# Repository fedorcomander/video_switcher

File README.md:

# video_switcher
4 channel FPV video switcher

Components: ATTINY85 and 4066

PCB: https://oshpark.com/shared_projects/mzDZTLOi

Video: https://youtu.be/O_MsIK6PSBA

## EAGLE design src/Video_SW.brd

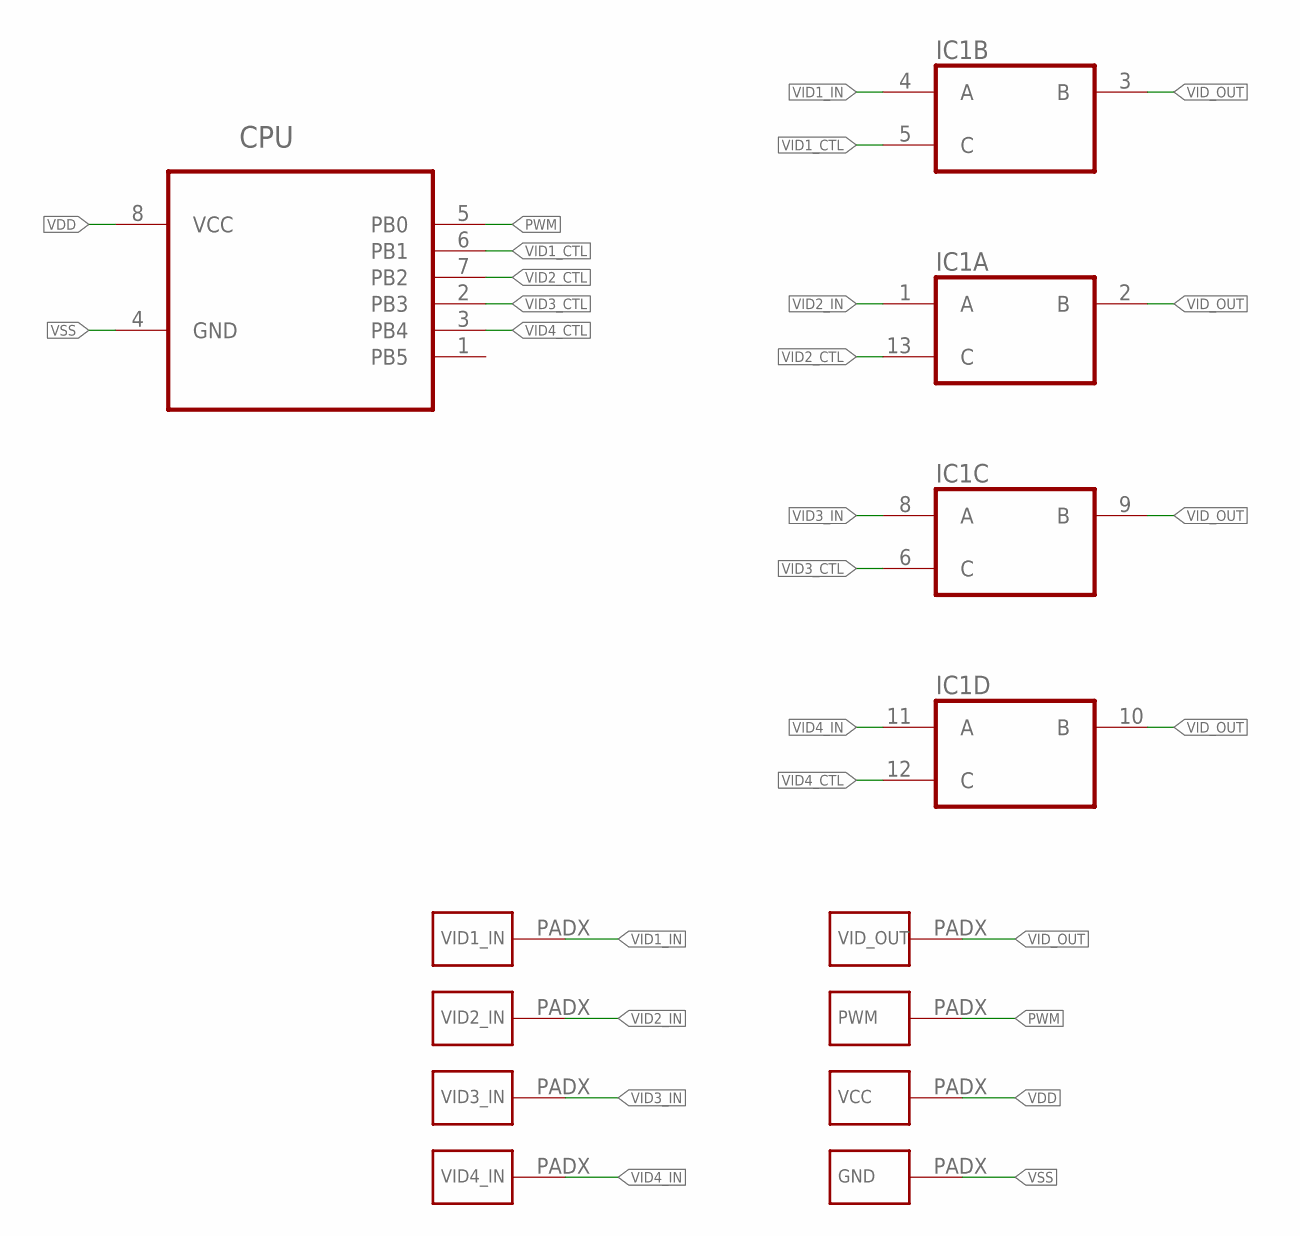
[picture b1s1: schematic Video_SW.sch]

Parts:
CPU: ATTINY85-20SU; SOIC127P798X216-8N
GND: SOLDERPAD
IC1: 4066D; SO14
PWM: SOLDERPAD
VCC: SOLDERPAD
VID1_IN, VID2_IN, VID3_IN, VID4_IN: SOLDERPAD
VID_OUT: SOLDERPAD

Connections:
PWM: CPU.5 (PB0), PWM.PADX
VDD: CPU.8 (VCC), IC1.14 (VDD), VCC.PADX
VID1_CTL: CPU.6 (PB1), IC1.5 (C)
VID1_IN: IC1.4 (A), VID1_IN.PADX
VID2_CTL: CPU.7 (PB2), IC1.13 (C)
VID2_IN: IC1.1 (A), VID2_IN.PADX
VID3_CTL: CPU.2 (PB3), IC1.6 (C)
VID3_IN: IC1.8 (A), VID3_IN.PADX
VID4_CTL: CPU.3 (PB4), IC1.12 (C)
VID4_IN: IC1.11 (A), VID4_IN.PADX
VID_OUT: IC1.2 (B), IC1.3 (B), IC1.9 (B), IC1.10 (B), VID_OUT.PADX
VSS: CPU.4 (GND), GND.PADX, IC1.7 (VSS)

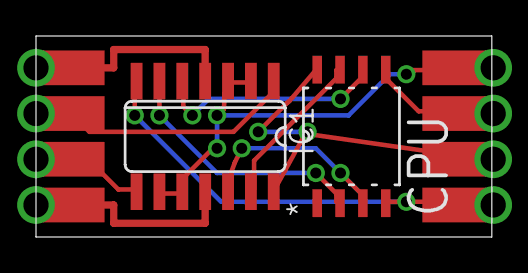
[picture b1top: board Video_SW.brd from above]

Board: 2 copper layers, 25.3 x 11.2 mm, 10 parts (0 on the bottom side), 12 nets.

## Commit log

2018-04-20 Initial import
2018-04-20 Added eagle files
